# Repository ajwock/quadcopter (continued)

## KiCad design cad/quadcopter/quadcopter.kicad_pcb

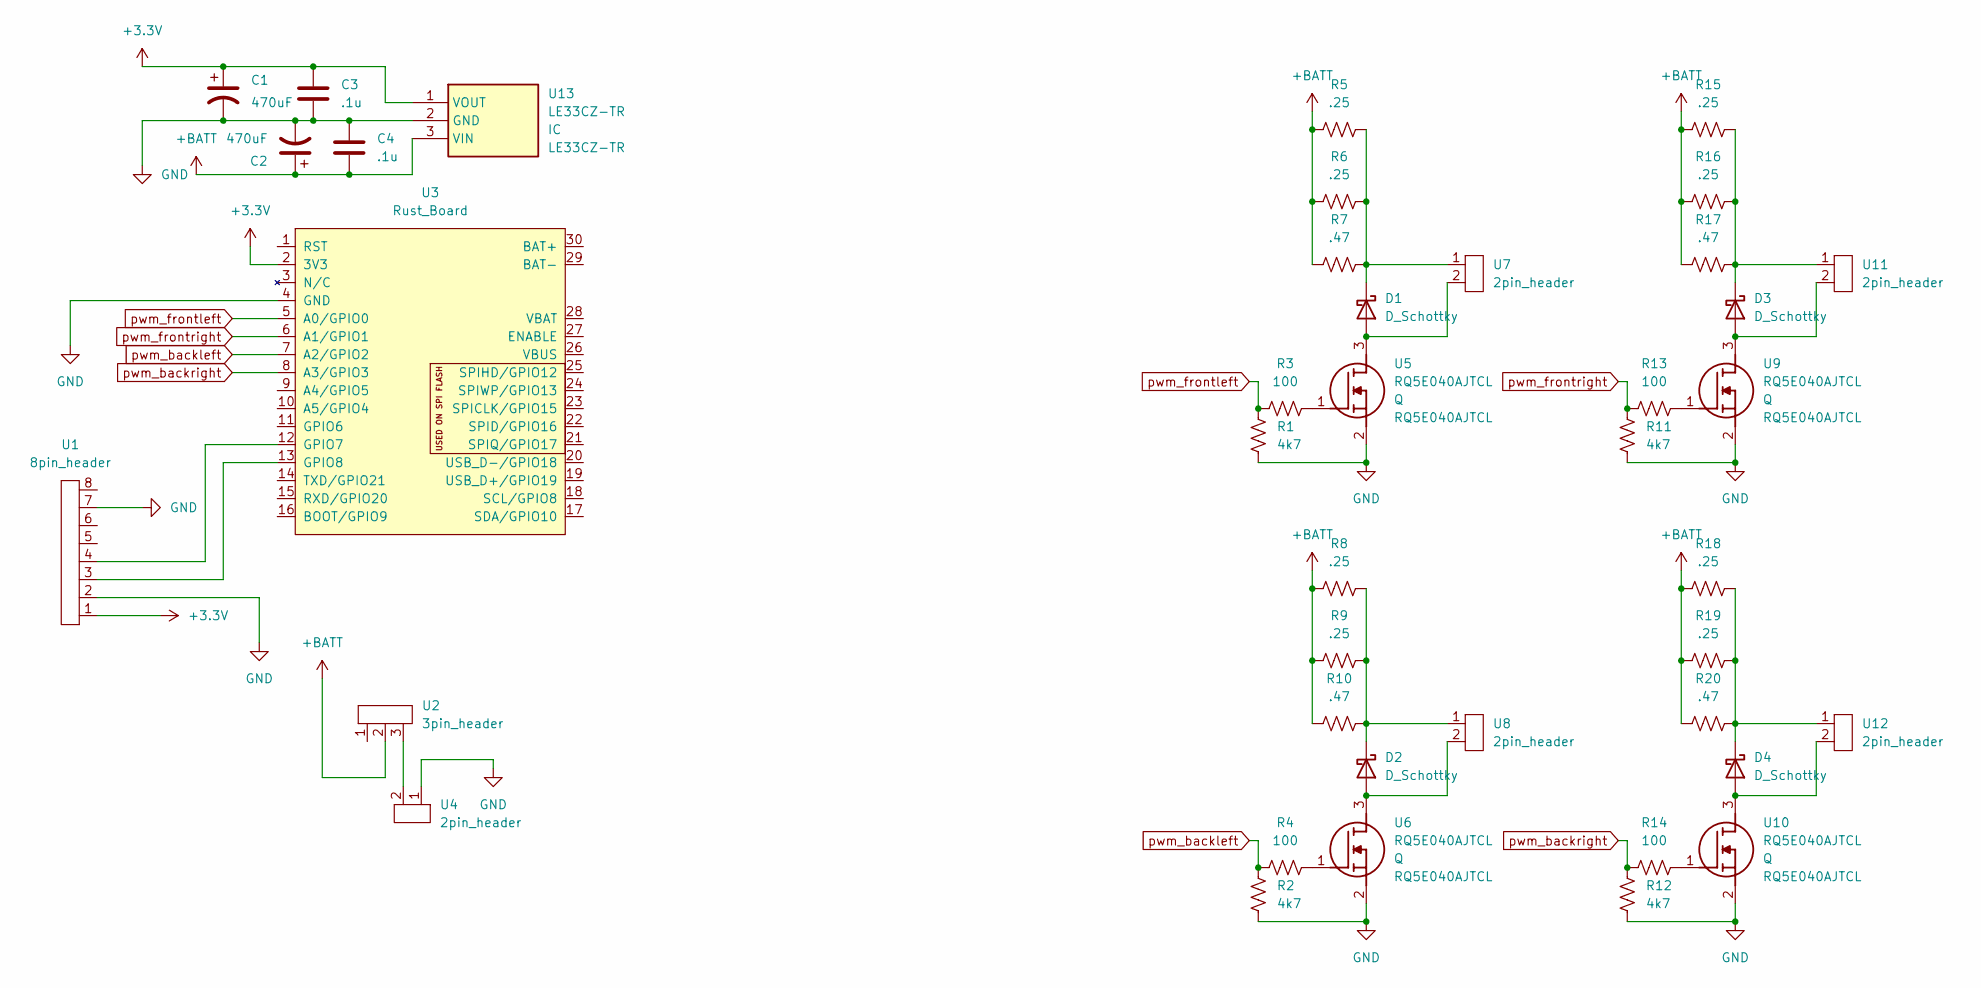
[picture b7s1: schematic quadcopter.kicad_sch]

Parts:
C1, C2: 470uF; CP_Radial_D6.3mm_P2.50mm
C3, C4: .1u; C_0603_1608Metric_Pad1.08x0.95mm_HandSolder
D1, D2, D3, D4: D_Schottky; SM6F22AY
R1, R2, R11, R12: 4k7; R_0603_1608Metric
R3, R4, R13, R14: 100; R_0603_1608Metric
R5, R6, R8, R9, R15, R16, R18, R19: .25; R_0805_2012Metric
R7, R10, R17, R20: .47; R_Axial_DIN0309_L9.0mm_D3.2mm_P12.70mm_Horizontal
U1: 8pin_header; 8-bb
U2: 3pin_header; 3-bb
U3: Rust_Board
U4, U7, U8, U11, U12: 2pin_header; 2-bb
U5, U6, U9, U10: RQ5E040AJTCL; SOT95P280X100-3N; Mouser Part Number 755-RQ5E040AJTCL
U13: LE33CZ-TR; LE33CZTR; Mouser Part Number 511-LE33CZ-TR

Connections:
+3.3V: C1.1, C3.1, U1.1, U3.2 (3V3), U13.1 (VOUT)
+BATT: C2.1, C4.2, R5.1, R6.1, R7.1, R8.1, R9.1, R10.1, R15.1, R16.1, R17.1, R18.1, R19.1, R20.1, U2.2, U13.3 (VIN)
GND: C1.2, C2.2, C3.2, C4.1, R1.2, R2.2, R11.2, R12.2, U1.2, U1.7, U3.4 (GND), U4.1, U5.2 (S), U6.2 (S), U9.2 (S), U10.2 (S), U13.2 (GND)
unnamed: D1.1 (K), R5.2, R6.2, R7.2, U7.1
unnamed: D1.2 (A), U5.3 (D), U7.2
unnamed: D2.1 (K), R8.2, R9.2, R10.2, U8.1
unnamed: D2.2 (A), U6.3 (D), U8.2
unnamed: D3.1 (K), R15.2, R16.2, R17.2, U11.1
unnamed: D3.2 (A), U9.3 (D), U11.2
unnamed: D4.1 (K), R18.2, R19.2, R20.2, U12.1
unnamed: D4.2 (A), U10.3 (D), U12.2
unnamed: R3.2, U5.1 (G)
unnamed: R4.2, U6.1 (G)
unnamed: R13.2, U9.1 (G)
unnamed: R14.2, U10.1 (G)
unnamed: U1.3, U3.13 (GPIO8)
unnamed: U1.4, U3.12 (GPIO7)
unnamed: U2.3, U4.2
pwm_backleft: R2.1, R4.1, U3.7 (A2/GPIO2)
pwm_backright: R12.1, R14.1, U3.8 (A3/GPIO3)
pwm_frontleft: R1.1, R3.1, U3.5 (A0/GPIO0)
pwm_frontright: R11.1, R13.1, U3.6 (A1/GPIO1)

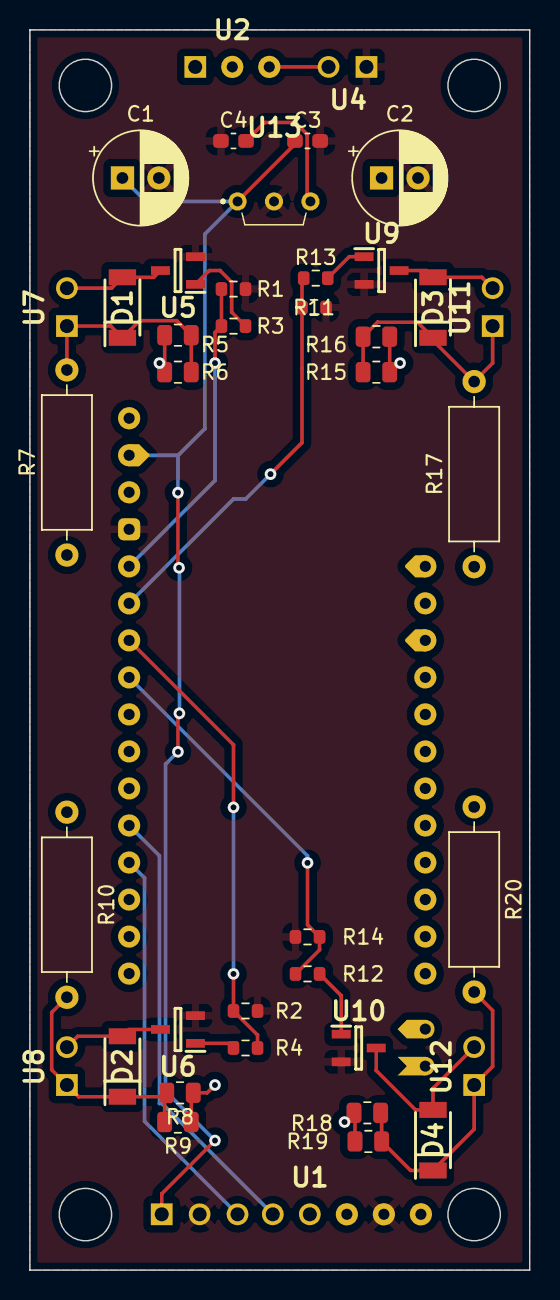
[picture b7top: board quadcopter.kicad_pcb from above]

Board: 2 copper layers, 34.3 x 85.1 mm, 41 parts (0 on the bottom side), 22 nets.

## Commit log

2025-03-08 Initial commit. mpu-6050 functioning
2025-03-08 Encapsulated Mpu6050 logic as a struct
2025-03-08 Mid-async change commit
2025-03-08 added debug script
2025-03-08 Transitional period as I figure out how to make pwms thread safe?
2025-03-08 Motor drive refactor
2025-03-09 Some buggy stabilization code done
2025-03-09 Corrected normalization code
2025-03-09 Added accelerometer/gyro calibration
2025-03-11 Used _async versions of methods, got same bugs
2025-03-12 uart interrupt written but going a different direction now
2025-03-12 Another bad uart implementation of control messages... deleting it now lol
2025-03-14 Took away uart reciever
2025-03-15 Added ecad files v1
2025-03-15 Realized the error in my footprints...
2025-03-16 Added several boards
2025-03-17 Tweaks to quad_direct eval board
2025-03-23 Getting a true async version up
2025-03-23 Added imu common to main
2025-03-23 stepping forth, trying to use esp as a network access point for control purposes
2025-03-23 works on mine
2025-03-24 Fixed async i2c issue... somewhat
2025-03-24 fixed the hal driver lol
2025-03-24 Cad changes
2025-03-25 increased motion frequency...
2025-03-28 Big progress saver
2025-03-28 gyro correction implemented
2025-03-29 Preparing to massively revamp my attitude control code to be based on angles instead of unit vector
2025-03-29 angular
2025-03-31 Preparing more advanced imu driver for integrating more gyro data
2025-03-31 Messy driver so far but the fifo works
2025-04-01 Placeholder commit...
2025-04-04 progress on orientation tracking
2025-04-04 temp cad
2025-04-05 Makera setup
2025-04-07 Added msg api to imu_common
2025-04-07 Added Carvera pcb files
2025-04-08 So the math is funky but hey, integrated gyro data seems to work
2025-04-08 fallibleified
2025-04-09 uhhhhhh
2025-04-18 boardy boards
2025-04-23 homecopter
2025-04-24 pre-homecopter change updates
2025-04-24 Homecopter rev3
2025-04-25 realized a major improvement, saving progress
2025-04-28 Likely hand solderable copter pcb finally designed!
2025-04-30 Got a working board design, and changed to code to align with it
2025-04-30 First semblance of stable flightgit add .git add .!
2025-05-02 Saving the tuning before derivative overhaul
2025-05-02 Derivative correction based on orientation diff, not error diff
2025-05-02 print cleanups and test flight routine added
2025-05-02 Full PID loop implemented and reasonably well tuned
2025-05-03 Enhanced automated test routine and dampened rotational correction
2025-05-03 Latest test flight routine
2025-05-03 Added iniitial remote control capabilities over AP-mode wifi
2025-05-04 Some messy rendition of what speed control might look like... very messy
2025-05-04 Fixed large bug with lateral movement
2025-05-06 One minute lemme try something
2025-05-06 Reworked the orientation tracking code to be more clear, maybe
2025-05-07 Uhh I don't actually think this is a good tree to bark up
2025-05-08 Working on latest frame
2025-05-08 Heavy frame. Too heavy and eats up battery but produced wonderfully stable flight briefly
2025-05-09 Another frame iteration
2025-05-11 Trying to make control a bit smoother
2025-05-11 gitignore cad backup zip files
2025-05-11 Cleanup...
2025-05-11 Sensor fusion: complementary filter between accel and gyro
2025-05-11 aaaaa
2025-05-12 Actual cringe fail
2025-05-12 Now this branch flies with the fusion
2025-05-17 Sketchy stm imu example
2025-05-17 proximity sensor board designed
2025-05-17 Maybe fixed build for other machines?
2025-05-19 Reorganizing quadcopter into a monorepo for some future deps
2025-05-21 Added icm42670 pac
2025-05-22 icm42670p_pac added, continuing to rework icm42670 driver
2025-05-22 icm42670 test hangs..
2025-05-22 Now using icm42670 driver for orientation tracking
2025-05-23 Quadframe 4 initial iteration, flew well but fragile, needs fillets
2025-05-23 Quadframe4 Tweaked...
2025-05-23 lsm6dsv pac progress, standard registers
2025-05-24 Progress on lsm6dsv pac
2025-05-24 lsm progress
2025-05-25 First great flight. Quite a bit behind some changes which were also good though.
2025-05-25 First great flight: Re-added complementary filter with accel hardware lowpassed
2025-05-25 Resolved warnings, did a lot of dead code cleanup
2025-05-25 Actually trying to troubleshoot why this isn't as good as older version
2025-05-25 Regened code
2025-05-26 Old driver, new code. Great flight
2025-05-26 AAAAA one mmoment
2025-05-26 Error handling in icm42670_imu improved
2025-05-27 Old config, new runtime data reading. Still have the error
2025-05-27 New driver configures, old driver works at runtime. Flight is good.
2025-05-27 Great flight with new driver! Jank flight caused by async yield in main interrupt loop
2025-05-27 initial orientation detection
2025-05-27 Added collective scaling for PID correction
2025-05-27 New frame iterations
2025-05-27 Converted to spi-based 24Mhz communications
2025-05-27 Removed unneccessary tilt calculations
2025-05-27 Refactored networking tasks from main to separate file
2025-05-27 Tightened PID loop to 120 ticks per second
2025-05-27 Significantly tempered derivative correction leads to massive stability boost
2025-05-27 Gentler gyro drift compensation leads to less veering during flight
2025-05-27 Full PID loop for rotation
2025-05-27 Sorta like this tuning actually, but needs work
2025-05-27 Okay, good rot tuning for real
2025-05-27 Proportional favoring retune
2025-05-27 .9p, .02i, .45d good precision flying tune
2025-05-27 Great tuning for both hovering and more aggressive flying, slow to converge to vertical hover
2025-05-27 Added rotational controls
2025-05-28 Clamp on position tighter to prevent wobbling out of control
2025-05-29 Another tuning I think I like more
2025-05-29 More granular collective power control
2025-05-29 Major improvement to piloting with granular collective control
2025-05-29 333Hz pid
2025-05-29 Made most things independent of pid loop speed at const time, tweaked to 500Hz
2025-05-29 Added tcp controller to repo
2025-05-29 Reworked LED pattern and refactored duplication into DigitalPLL struct
2025-05-29 Removing unnecessary temp files
2025-05-29 Removed gcode files
2025-06-02 First pass at getting cam module, pin ordering on fpc-connector reversed
2025-08-11 Added s3cam pcbs
2025-08-12 First 3d model of ball joint, needs better outer joint grip
2025-08-18 Gimbal assembly v2
    Contains hinge and cap in assembly
2025-08-18 Added servomotor driving example for c3
2026-05-31 Adding controller to github
